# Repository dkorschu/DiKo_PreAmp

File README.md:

# $\text{-DIKO-}\sqrt{\text{REGGAE}}\text{-PREAMP-}$

[English version below](#english-version)

Dieses Repository zeigt die Entwicklung des DIKO ELEKTROTECHNIK Vorverstärkers, vom ersten Prototyp bis zum aktuellen Stand.

## Ordnerstruktur

- Blockschaltbilder
- Ältere Versionen
- KiCad Dateien
- Bilder
- Datenblätter
- 3D Druck

## Version 1

Version 1 entstand im Rahmen meiner Bachelorarbeit. Schaltpläne und Fertigungsdateien der Platinen wurden mit Altium Designer erstellt. Das Besondere an dieser Version: Die analoge Frequenzweiche lässt sich über Digitalpotentiometer einstellen.

**Hinweis: Version 1 ist fehlerhaft!**

## Version 2

Version 2 baut auf den Erkenntnissen aus Version 1 auf und bringt komplett neue Platinen mit. Die Digitalpotentiometer sind entfallen, da der Vorverstärker einfacher werden und der Fokus zunächst auf der analogen Schaltungstechnik liegen sollte. Zur Berechnung der Frequenzweiche wurden außerdem Jupyter Notebooks eingesetzt, die sehr gute Ergebnisse geliefert haben.

Bei den bisherigen Tests wurden schaltungstechnisch keine Fehler gefunden. Trotzdem gibt es zwei Schwachstellen:

- Das Platinenlayout ist nicht zufriedenstellend.
- Der Mikrofonvorverstärker verstärkt das Signal nicht ausreichend.

Aus diesen Gründen wird nun an Version 3 gearbeitet.

## Version 3

Version 3 teilt den Vorverstärker in einzelne Komponenten auf, die sich miteinander verbinden lassen.

2026_10_05 Den Anfang macht die Frequenzweiche, die sich auch eigenständig mit einem externen Mischpult nutzen lässt.

---

# English Version

This repository documents the development of the DIKO ELEKTROTECHNIK preamplifier, from the first prototype to the current state.

## Folder Structure

- Blockschaltbilder (block diagrams)
- Ältere Versionen (older versions)
- KiCad Dateien (KiCad files)
- Bilder (images)
- Datenblätter (datasheets)
- 3D Druck (3D printing)

## Version 1
Version 1 was developed as part of my bachelor's thesis. The schematics and PCB manufacturing files were created with Altium Designer. What makes this version special: the analog crossover can be adjusted using digital potentiometers.

**Note: Version 1 is faulty!**

## Version 2

Version 2 builds on the findings from Version 1 and comes with completely new PCBs. The digital potentiometers were removed to make the preamp simpler and to focus on the analog circuitry first. In addition, Jupyter Notebooks were used to calculate the crossover, with very good results.

So far, testing has not revealed any circuit errors. However, there are two weak points:

- The PCB layout is not satisfactory.
- The microphone preamp does not amplify the signal sufficiently.

For these reasons, work is now underway on Version 3.

## Version 3

Version 3 splits the preamp into individual components that can be connected to each other.

2026_10_05 The first step is the crossover, which can also be used on its own with an external mixing console.

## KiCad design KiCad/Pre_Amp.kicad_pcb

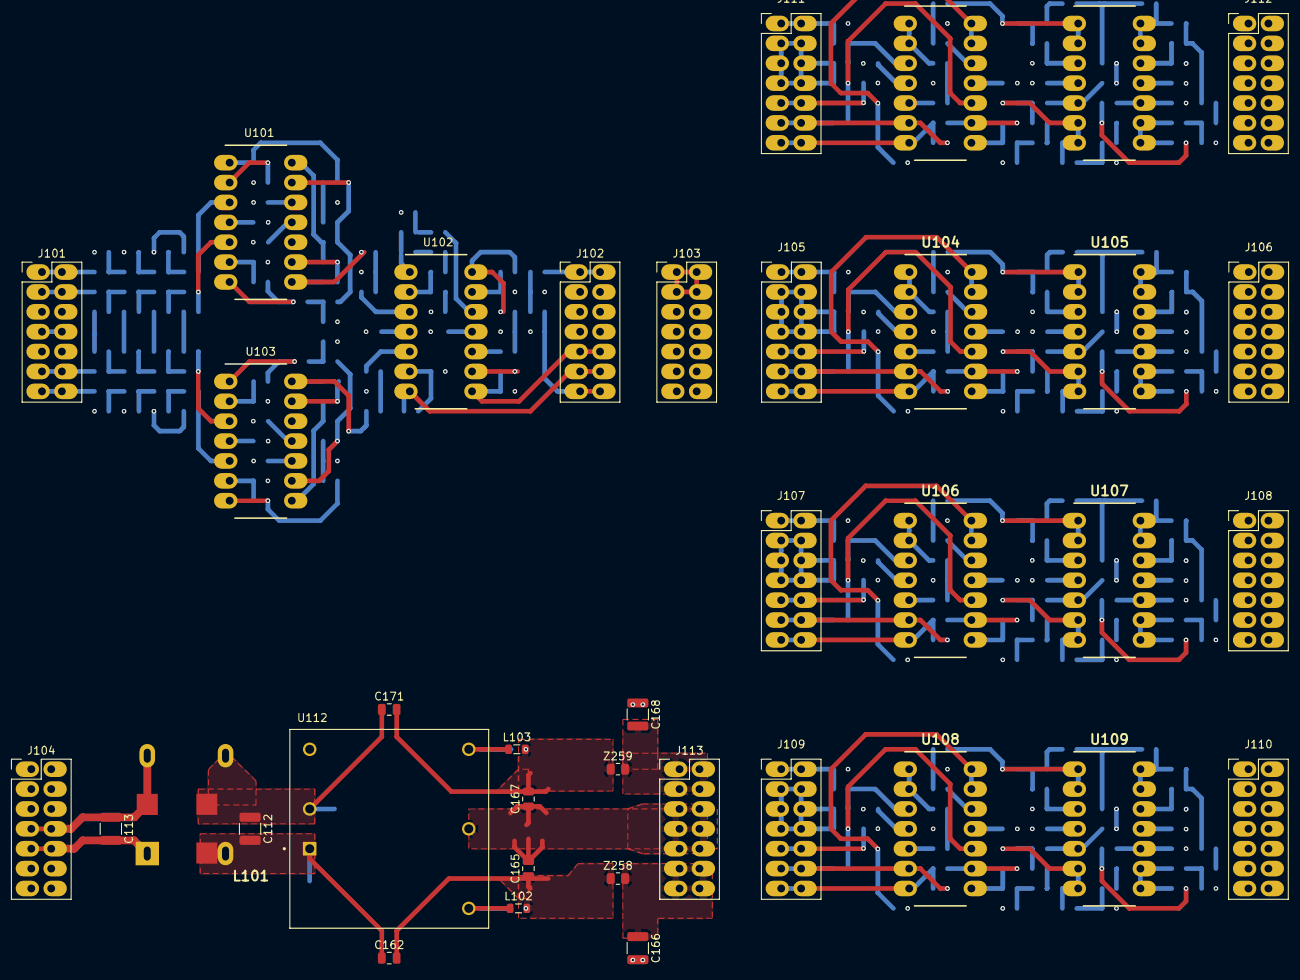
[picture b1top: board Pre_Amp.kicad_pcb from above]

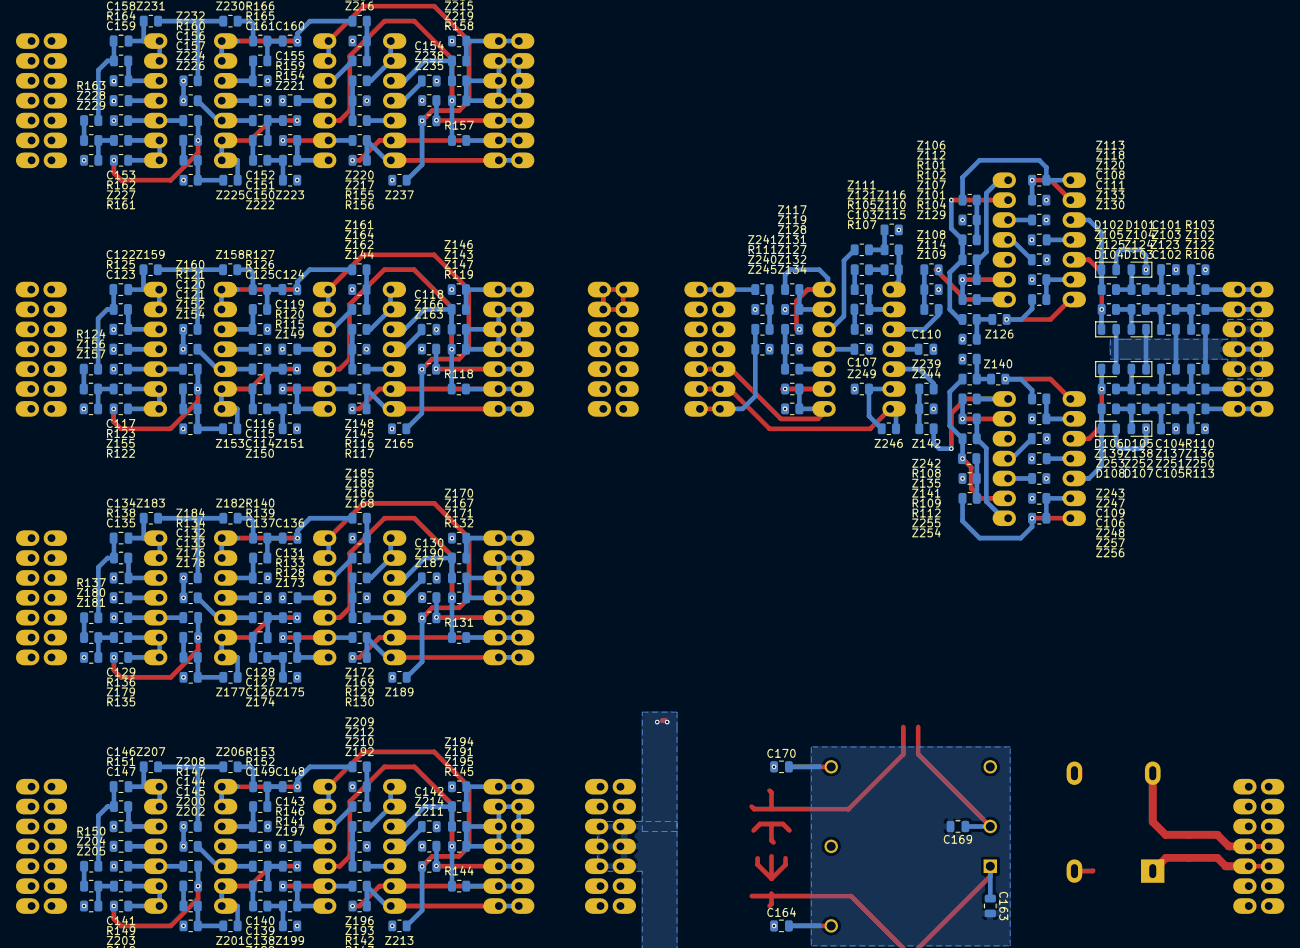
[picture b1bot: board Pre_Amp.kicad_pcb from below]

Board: 4 copper layers, 331 parts (293 on the bottom side), 210 nets.

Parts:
C101, C102, C104, C105, C114, C115, C126, C127, C138, C139, C150, C151, C163, C169: 10n; C_0805_2012Metric
C103: 47u; C_0805_2012Metric
C106, C107, C108, C109, C110, C111, C116, C117, C118, C119, C125, C128, C129, C130, C131, C137, C140, C141, C142, C143, C149, C152, C153, C154, C155, C161, C165, C167: 100n; C_0805_2012Metric
C112, C113, C166, C168: 10u; C_1210_3225Metric
C120, C121, C132, C133, C144, C145, C156, C157: 220n; C_0805_2012Metric
C122, C123, C134, C135, C146, C147, C158, C159: 150n; C_0805_2012Metric
C124, C136, C148, C160: 1u; C_0805_2012Metric
C162, C171: 470p; C_0805_2012Metric
C164, C170: 1n; C_0805_2012Metric
D101, D102, D103, D104, D105, D106, D107, D108: D; D_0805_2012Metric
J101: Stecker_4In; PinHeader_2x07_P2.54mm_Vertical
J102: Stecker_1Out_Switch; PinHeader_2x07_P2.54mm_Vertical
J103, J106, J108, J110, J112: Conn_02x07_Odd_Even; PinHeader_2x07_P2.54mm_Vertical
J104: Stecker_1In_2Switch; PinHeader_2x07_P2.54mm_Vertical
J105, J107, J109, J111: Stecker_In_Out_Switch; PinHeader_2x07_P2.54mm_Vertical
J113: VCC; PinHeader_2x07_P2.54mm_Vertical
L101: WE-SL575
L102, L103: Dämpfungsperle, 220 Ohm @ 100MHz, 0.5A; L_0805_2012Metric
R101, R102, R104, R108, R109, R112, R122, R135, R148, R161: 10k; R_0805_2012Metric
R103, R106, R110, R111, R113: 390k; R_0805_2012Metric
R105: 33k; R_0805_2012Metric
R107, R116, R117, R118, R129, R130, R131, R142, R143, R144, R155, R156, R157: 1k; R_0805_2012Metric
R115, R119, R128, R132, R141, R145, R154, R158: 100k; R_0805_2012Metric
R120, R133, R146, R159: 560k; R_0805_2012Metric
R121, R134, R147, R160: 680k; R_0805_2012Metric
R123, R136, R149, R162: 75k; R_0805_2012Metric
R124, R125, R137, R138, R150, R151, R163, R164: 15k; R_0805_2012Metric
R126, R127, R139, R140, R152, R153, R165, R166: 7k5; R_0805_2012Metric
U101, U102, U103, U104, U105, U106, U107, U108, U109, U110, U111: TL074; DIP794W53P254L1930H508Q14N
U112: REC10K-2415; CONV_REC10K-2415DAW_H2
Z101, Z102, Z103, Z104, Z105, Z106, Z107, Z112, Z113, Z117, Z118, Z119, Z120, Z122, Z123, Z124, Z125, Z126, Z129, Z130, Z132, Z133, Z134, Z135, Z136, Z137, Z138, Z139, Z140, Z141, Z146, Z148, Z151, Z154, Z160, Z165, Z170, Z172, Z175, Z178, Z184, Z189, Z194, Z196, Z199, Z202, Z208, Z213, Z218, Z220, Z223, Z226, Z232, Z237, Z240, Z241, Z242, Z243, Z245, Z246, Z247, Z248, Z249, Z250, Z251, Z252, Z253, Z254, Z255, Z256, Z257: R_0805_2012Metric
Z108, Z109, Z110, Z111, Z127, Z128, Z142, Z144, Z145, Z149, Z150, Z152, Z153, Z155, Z156, Z158, Z159, Z161, Z162, Z168, Z169, Z173, Z174, Z176, Z177, Z179, Z180, Z182, Z183, Z185, Z186, Z192, Z193, Z197, Z198, Z200, Z201, Z203, Z204, Z206, Z207, Z209, Z210, Z216, Z217, Z221, Z222, Z224, Z225, Z227, Z228, Z230, Z231, Z233, Z234, Z239, Z258, Z259: 0R; R_0805_2012Metric
Z114, Z116, Z131, Z157, Z164, Z181, Z188, Z205, Z212, Z229, Z236, Z244: 820k; R_0805_2012Metric
Z115: 390k/10n; R_0805_2012Metric
Z121: 33k/2n2; R_0805_2012Metric
Z143, Z163, Z167, Z187, Z191, Z211, Z215, Z235: 1u; R_0805_2012Metric
Z147, Z166, Z171, Z190, Z195, Z214, Z219, Z238: 100k; R_0805_2012Metric

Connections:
+15V: C106.2, C108.2, C110.2, C116.2, C118.2, C128.2, C130.2, C140.2, C142.2, C152.2, C154.2, C166.1, J103.11, J103.12, J103.13, J103.14, J106.11, J106.12, J106.13, J106.14, J108.11, J108.12, J108.13, J108.14, J110.11, J110.12, J110.13, J110.14, J112.11, J112.12, J112.13, J112.14, J113.11 (+15V), J113.12 (+15V), J113.13 (+15V), J113.14 (+15V), U101.4 (V+), U102.4 (V+), U103.4 (V+), U104.4 (V+), U105.4 (V+), U106.4 (V+), U107.4 (V+), U108.4 (V+), U109.4 (V+), U110.4 (V+), U111.4 (V+), Z258.2
-15V: C107.2, C109.2, C111.2, C117.2, C119.2, C129.2, C131.2, C141.2, C143.2, C153.2, C155.2, C168.2, J103.1, J103.2, J103.3, J103.4, J106.1, J106.2, J106.3, J106.4, J108.1, J108.2, J108.3, J108.4, J110.1, J110.2, J110.3, J110.4, J112.1, J112.2, J112.3, J112.4, J113.1 (-15V), J113.2 (-15V), J113.3 (-15V), J113.4 (-15V), U101.11 (V-), U102.11 (V-), U103.11 (V-), U104.11 (V-), U105.11 (V-), U106.11 (V-), U107.11 (V-), U108.11 (V-), U109.11 (V-), U110.11 (V-), U111.11 (V-), Z259.2
GND: C101.1, C102.1, C104.1, C105.1, C106.1, C107.1, C108.1, C109.1, C110.1, C111.1, C116.1, C117.1, C118.1, C119.1, C123.1, C125.1, C128.1, C129.1, C130.1, C131.1, C135.1, C137.1, C140.1, C141.1, C142.1, C143.1, C147.1, C149.1, C152.1, C153.1, C154.1, C155.1, C159.1, C161.1, C165.2, C166.2, C167.1, C168.1, D101.1 (K), D102.2 (A), D103.1 (K), D104.2 (A), D105.1 (K), D106.2 (A), D107.1 (K), D108.2 (A), J101.5 (GND), J101.6 (GND), J101.7 (GND), J101.8 (GND), J101.9 (GND), J101.10 (GND), J102.3 (GND), J102.4 (GND), J102.5 (GND), J102.6 (GND), J102.7 (GND), J102.8 (GND), J103.5, J103.6, J103.7, J103.8, J103.9, J103.10, J105.3, J105.4, J105.5, J105.6, J105.7, J105.8, J106.5, J106.6, J106.7, J106.8, J106.9, J106.10, J107.3, J107.4, J107.5, J107.6, J107.7, J107.8, J108.5, J108.6, J108.7, J108.8, J108.9, J108.10, J109.3, J109.4, J109.5, J109.6, J109.7, J109.8, J110.5, J110.6, J110.7, J110.8, J110.9, J110.10, J111.3, J111.4, J111.5, J111.6, J111.7, J111.8, J112.5, J112.6, J112.7, J112.8, J112.9, J112.10, J113.5 (GND), J113.6 (GND), J113.7 (GND), J113.8 (GND), J113.9 (GND), J113.10 (GND), R103.2, R106.2, R107.1, R110.2, R111.2, R113.2, R119.1, R121.1, R123.1, R132.1, R134.1, R136.1, R145.1, R147.1, R149.1, R158.1, R160.1, R162.1, U101.10 (+), U103.12 (+), U112.5 (COM), Z112.2, Z114.2, Z116.2, Z118.2, Z119.2, Z120.2, Z129.2, Z131.2, Z133.2, Z134.2, Z146.2, Z147.2, Z148.2, Z151.2, Z154.2, Z157.2, Z160.2, Z164.2, Z165.2, Z166.2, Z170.2, Z171.2, Z172.2, Z175.2, Z178.2, Z181.2, Z184.2, Z188.2, Z189.2, Z190.2, Z194.2, Z195.2, Z196.2, Z199.2, Z202.2, Z205.2, Z208.2, Z212.2, Z213.2, Z214.2, Z218.2, Z219.2, Z220.2, Z223.2, Z226.2, Z229.2, Z232.2, Z236.2, Z237.2, Z238.2, Z242.2, Z244.2, Z245.2, Z247.2, Z248.2, Z249.2, Z255.2, Z257.2
GND_FILT: C163.2, C164.2, C169.2, C170.2
unnamed: C101.2, Z103.2, Z104.1
unnamed: C102.2, Z123.2, Z124.1
unnamed: C103.1, R107.2
unnamed: C104.2, Z137.2, Z138.1
unnamed: C105.2, Z251.2, Z252.1
unnamed: C113.1, J104.7 (SW_2), J104.8 (SW_2), L101.4
unnamed: C113.2, J104.9 (SW_4), J104.10 (SW_4), L101.1
unnamed: C114.1, Z150.1
unnamed: C114.2, C115.1, R120.1
unnamed: C120.1, C121.2, R122.1
unnamed: C121.1, Z152.2
unnamed: C122.1, R124.2, R125.1
unnamed: C124.1, R126.1, R127.2
unnamed: C126.1, Z174.1
unnamed: C126.2, C127.1, R133.1
unnamed: C132.1, C133.2, R135.1
unnamed: C133.1, Z176.2
unnamed: C134.1, R137.2, R138.1
unnamed: C136.1, R139.1, R140.2
unnamed: C138.1, Z198.1
unnamed: C138.2, C139.1, R146.1
unnamed: C144.1, C145.2, R148.1
unnamed: C145.1, Z200.2
unnamed: C146.1, R150.2, R151.1
unnamed: C148.1, R152.1, R153.2
unnamed: C150.1, Z222.1
unnamed: C150.2, C151.1, R159.1
unnamed: C156.1, C157.2, R161.1
unnamed: C157.1, Z224.2
unnamed: C158.1, R163.2, R164.1
unnamed: C160.1, R165.1, R166.2
unnamed: C162.2, C164.1, C165.1, L102.2, Z258.1
unnamed: C167.2, C170.1, C171.2, L103.2, Z259.1
unnamed: D101.2 (A), Z104.2, Z105.1
unnamed: D102.1 (K), U101.3 (+), Z105.2
unnamed: D103.2 (A), Z124.2, Z125.1
unnamed: D104.1 (K), U101.5 (+), Z125.2
unnamed: D105.2 (A), Z138.2, Z139.1
unnamed: D106.1 (K), U103.3 (+), Z139.2
unnamed: D107.2 (A), Z252.2, Z253.1
unnamed: D108.1 (K), U103.5 (+), Z253.2
unnamed: J101.1 (Phono_L), J101.2, Z102.1
unnamed: J101.3 (Phono_R), J101.4 (Phono_R), Z122.1
unnamed: J101.11 (Line_L), J101.12 (Line_L), Z136.1
unnamed: J101.13 (Line_R), J101.14 (Line_R), Z250.1
unnamed: J102.9 (SW_In1), J102.10 (SW_2), U102.8, Z132.2, Z134.1
unnamed: J102.11 (SW_In2), J102.12 (SW_3), U102.7, Z246.1
unnamed: J102.13 (SW_Out), J102.14 (SW_Out), Z240.2, Z245.1
unnamed: J104.3 (VCC_GND), J104.4 (VCC_GND), J104.5 (VCC_GND), J104.6 (VCC_GND), J104.11 (SW_1), J104.12 (SW_1)
unnamed: J104.1 (VCC_In), J104.2 (VCC_In), J104.13 (SW_3), J104.14 (SW_3)
unnamed: J102.1 (Out), J102.2 (Out), J105.1, J105.2, J107.1, J107.2, J109.1, J109.2, J111.1, J111.2, Z143.2, Z146.1, Z167.2, Z170.1, Z191.2, Z194.1, Z215.2, Z218.1, Z241.1
unnamed: J105.9, J105.10, Z163.2, Z166.1
unnamed: J105.11 (SW_In), J105.12, R117.1, R118.1, U104.6 (-)
unnamed: J105.13 (SW_Out), J105.14, R116.1, R117.2, U104.7
unnamed: J107.9, J107.10, Z187.2, Z190.1
unnamed: J107.11 (SW_In), J107.12, R130.1, R131.1, U106.6 (-)
unnamed: J107.13 (SW_Out), J107.14, R129.1, R130.2, U106.7
unnamed: J109.9, J109.10, Z211.2, Z214.1
unnamed: J109.11 (SW_In), J109.12, R143.1, R144.1, U108.6 (-)
unnamed: J109.13 (SW_Out), J109.14, R142.1, R143.2, U108.7
unnamed: J111.9, J111.10, Z235.2, Z238.1
unnamed: J111.11 (SW_In), J111.12, R156.1, R157.1, U110.6 (-)
unnamed: J111.13 (SW_Out), J111.14, R155.1, R156.2, U110.7
unnamed: R101.1, Z106.2, Z112.1
unnamed: R102.2, U101.14, Z107.2
unnamed: R103.1, Z102.2, Z103.1
unnamed: R104.1, Z126.2, Z129.1
unnamed: R105.1, Z121.2
unnamed: R106.1, Z122.2, Z123.1
unnamed: R108.1, Z140.2, Z242.1
unnamed: R109.2, U103.8, Z141.2
unnamed: R110.1, Z136.2, Z137.1
unnamed: R111.1, Z240.1, Z241.2
unnamed: R112.1, Z254.2, Z255.1
unnamed: R113.1, Z250.2, Z251.1
unnamed: R115.2, U104.8, Z149.2
unnamed: R124.1, Z156.1
unnamed: R127.1, Z158.2
unnamed: R128.2, U106.8, Z173.2
unnamed: R137.1, Z180.1
unnamed: R140.1, Z182.2
unnamed: R141.2, U108.8, Z197.2
unnamed: R150.1, Z204.1
unnamed: R153.1, Z206.2
unnamed: R154.2, U110.8, Z221.2
unnamed: R163.1, Z228.1
unnamed: R166.1, Z230.2
unnamed: U101.1, Z106.1, Z113.1
unnamed: U101.7, Z126.1, Z130.1
unnamed: U101.8, Z101.1, Z108.1
unnamed: U101.2 (-), Z113.2, Z118.1
unnamed: U101.6 (-), Z130.2, Z133.1
unnamed: U101.9 (-), Z101.2, Z107.1
unnamed: U101.12 (+), Z120.1
unnamed: R101.2, R102.1, R104.2, U101.13 (-)
unnamed: U102.1, Z110.1, Z115.1
unnamed: U102.14, Z117.1, Z128.1
unnamed: U102.3 (+), Z109.2
unnamed: C103.2, R105.2, U102.2 (-)
unnamed: U102.5 (+), Z239.2
unnamed: U102.6 (-), Z246.2, Z249.1
unnamed: U102.10 (+), Z127.2
unnamed: U102.9 (-), Z132.1
unnamed: U102.12 (+), Z111.2
unnamed: U102.13 (-), Z117.2, Z119.1
unnamed: U103.1, Z140.1, Z243.1
unnamed: U103.7, Z254.1, Z256.1
unnamed: U103.14, Z135.1, Z142.1
unnamed: U103.2 (-), Z243.2, Z247.1
unnamed: U103.6 (-), Z256.2, Z257.1
unnamed: U103.10 (+), Z248.1
unnamed: R108.2, R109.1, R112.2, U103.9 (-)
unnamed: U103.13 (-), Z135.2, Z141.1
unnamed: U104.3 (+), Z143.1, Z147.1
unnamed: U104.1, U104.2 (-), Z144.2
unnamed: U104.5 (+), Z145.1
unnamed: R118.2, R119.2, U104.10 (+)
unnamed: R115.1, R116.2, U104.9 (-)
unnamed: U104.12 (+), Z162.2
unnamed: U104.13 (-), U104.14, Z163.1, Z165.1
unnamed: C125.2, R126.2, U105.3 (+)
unnamed: C124.2, U105.1, U105.2 (-), Z161.1
unnamed: C115.2, R121.2, U105.5 (+)
unnamed: R120.2, U105.6 (-), U105.7, Z153.1
unnamed: C120.2, R123.2, U105.10 (+)
unnamed: R122.2, U105.8, U105.9 (-), Z155.2
unnamed: C123.2, R125.2, U105.12 (+)
unnamed: C122.2, U105.13 (-), U105.14, Z159.1
unnamed: U106.3 (+), Z167.1, Z171.1
unnamed: U106.1, U106.2 (-), Z168.2
unnamed: U106.5 (+), Z169.1
unnamed: R131.2, R132.2, U106.10 (+)
unnamed: R128.1, R129.2, U106.9 (-)
unnamed: U106.12 (+), Z186.2
unnamed: U106.13 (-), U106.14, Z187.1, Z189.1
unnamed: C137.2, R139.2, U107.3 (+)
unnamed: C136.2, U107.1, U107.2 (-), Z185.1
unnamed: C127.2, R134.2, U107.5 (+)
unnamed: R133.2, U107.6 (-), U107.7, Z177.1
unnamed: C132.2, R136.2, U107.10 (+)
unnamed: R135.2, U107.8, U107.9 (-), Z179.2
unnamed: C135.2, R138.2, U107.12 (+)
unnamed: C134.2, U107.13 (-), U107.14, Z183.1
unnamed: U108.3 (+), Z191.1, Z195.1
unnamed: U108.1, U108.2 (-), Z192.2
unnamed: U108.5 (+), Z193.1
unnamed: R144.2, R145.2, U108.10 (+)
unnamed: R141.1, R142.2, U108.9 (-)
unnamed: U108.12 (+), Z210.2
unnamed: U108.13 (-), U108.14, Z211.1, Z213.1
unnamed: C149.2, R152.2, U109.3 (+)
unnamed: C148.2, U109.1, U109.2 (-), Z209.1
unnamed: C139.2, R147.2, U109.5 (+)
unnamed: R146.2, U109.6 (-), U109.7, Z201.1
unnamed: C144.2, R149.2, U109.10 (+)
unnamed: R148.2, U109.8, U109.9 (-), Z203.2
unnamed: C147.2, R151.2, U109.12 (+)
unnamed: C146.2, U109.13 (-), U109.14, Z207.1
unnamed: U110.3 (+), Z215.1, Z219.1
unnamed: U110.1, U110.2 (-), Z216.2
unnamed: U110.5 (+), Z217.1
unnamed: R157.2, R158.2, U110.10 (+)
unnamed: R154.1, R155.2, U110.9 (-)
unnamed: U110.12 (+), Z234.2
unnamed: U110.13 (-), U110.14, Z235.1, Z237.1
unnamed: C161.2, R165.2, U111.3 (+)
unnamed: C160.2, U111.1, U111.2 (-), Z233.1
unnamed: C151.2, R160.2, U111.5 (+)
unnamed: R159.2, U111.6 (-), U111.7, Z225.1
unnamed: C156.2, R162.2, U111.10 (+)
unnamed: R161.2, U111.8, U111.9 (-), Z227.2
unnamed: C159.2, R164.2, U111.12 (+)
unnamed: C158.2, U111.13 (-), U111.14, Z231.1
unnamed: C112.2, C162.1, C163.1, L101.2, U112.1 (+VIN)
unnamed: L102.1, U112.6 (+VOUT)
unnamed: C112.1, C169.1, C171.1, L101.3, U112.2 (-VIN)
unnamed: L103.1, U112.4 (-VOUT)
unnamed: Z108.2, Z109.1, Z114.1
unnamed: Z110.2, Z111.1, Z116.1
unnamed: Z115.2, Z121.1
unnamed: Z127.1, Z128.2, Z131.1
unnamed: Z142.2, Z239.1, Z244.1
unnamed: Z144.1, Z145.2, Z148.1
unnamed: Z149.1, Z150.2, Z151.1
unnamed: Z152.1, Z153.2, Z154.1
unnamed: Z155.1, Z156.2, Z157.1
unnamed: Z158.1, Z159.2, Z160.1
unnamed: Z161.2, Z162.1, Z164.1
unnamed: Z168.1, Z169.2, Z172.1
unnamed: Z173.1, Z174.2, Z175.1
unnamed: Z176.1, Z177.2, Z178.1
unnamed: Z179.1, Z180.2, Z181.1
unnamed: Z182.1, Z183.2, Z184.1
unnamed: Z185.2, Z186.1, Z188.1
unnamed: Z192.1, Z193.2, Z196.1
unnamed: Z197.1, Z198.2, Z199.1
unnamed: Z200.1, Z201.2, Z202.1
unnamed: Z203.1, Z204.2, Z205.1
unnamed: Z206.1, Z207.2, Z208.1
unnamed: Z209.2, Z210.1, Z212.1
unnamed: Z216.1, Z217.2, Z220.1
unnamed: Z221.1, Z222.2, Z223.1
unnamed: Z224.1, Z225.2, Z226.1
unnamed: Z227.1, Z228.2, Z229.1
unnamed: Z230.1, Z231.2, Z232.1
unnamed: Z233.2, Z234.1, Z236.1

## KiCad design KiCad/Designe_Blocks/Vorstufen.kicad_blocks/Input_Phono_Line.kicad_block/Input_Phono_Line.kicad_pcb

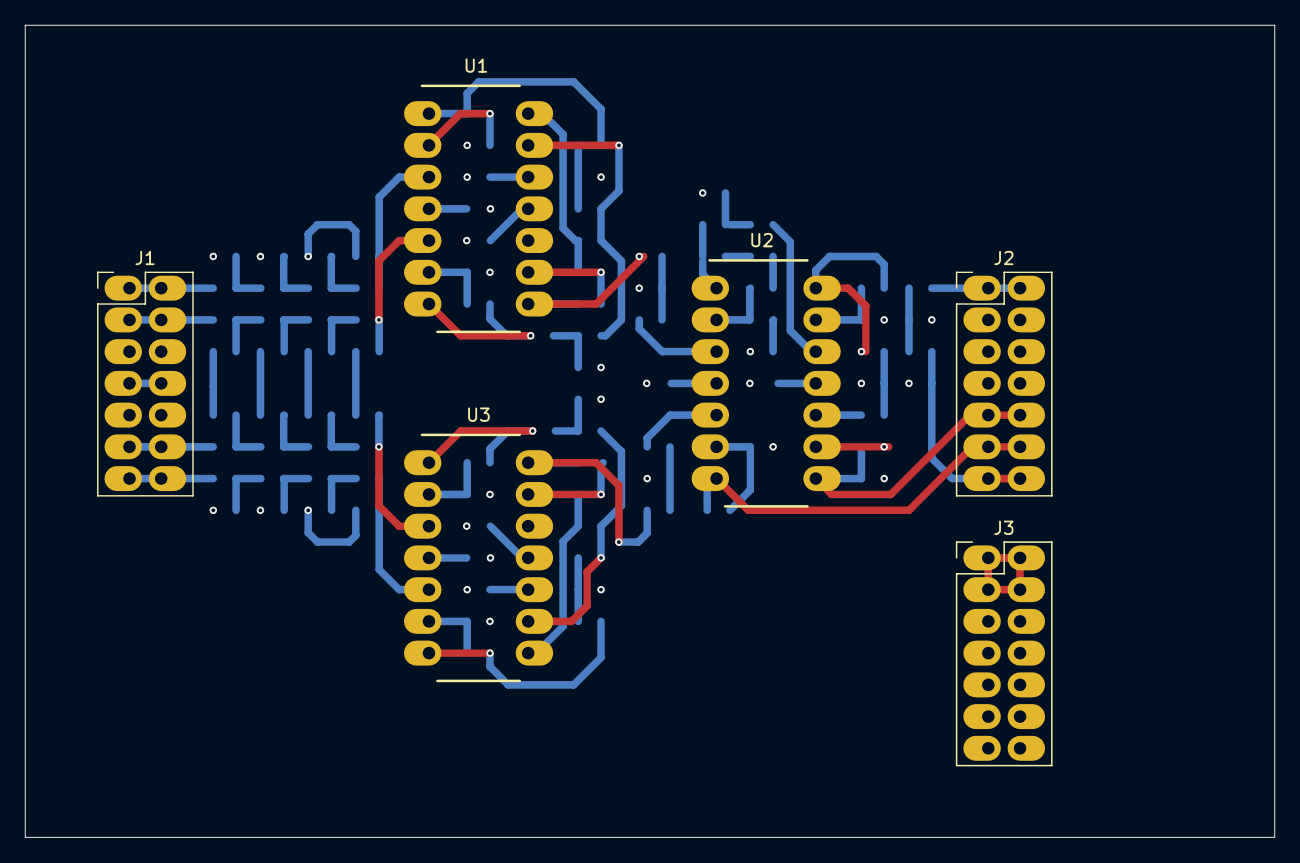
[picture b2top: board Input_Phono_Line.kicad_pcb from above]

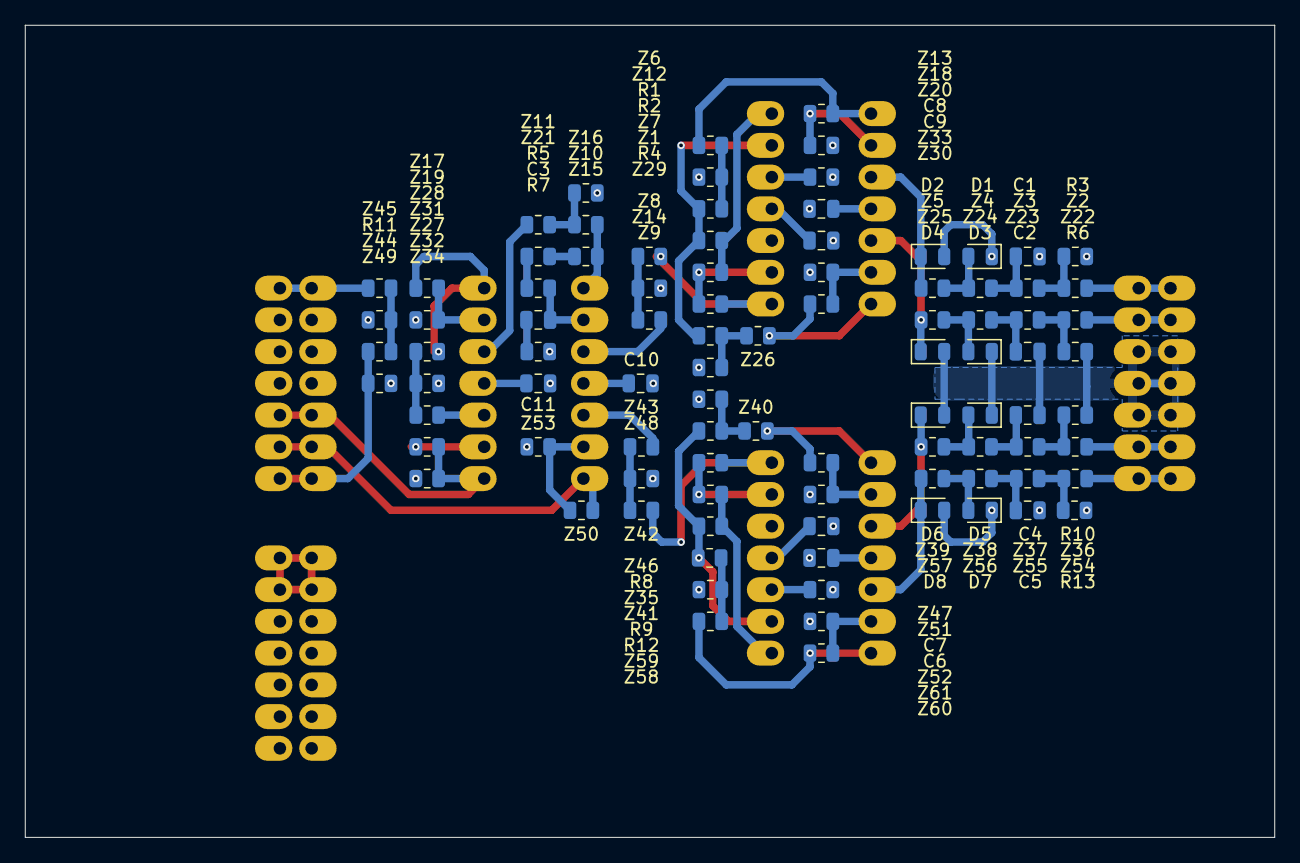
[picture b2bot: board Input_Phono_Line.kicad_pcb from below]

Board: 4 copper layers, 100.0 x 65.0 mm, 99 parts (93 on the bottom side), 67 nets.

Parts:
C1, C2, C4, C5: 10n; C_0805_2012Metric
C3: 47u; C_0805_2012Metric
C6, C7, C8, C9, C10, C11: 100n; C_0805_2012Metric
D1, D2, D3, D4, D5, D6, D7, D8: D; D_0805_2012Metric
J1: Stecker_4In; PinHeader_2x07_P2.54mm_Vertical
J2: Stecker_1Out_Switch; PinHeader_2x07_P2.54mm_Vertical
J3: Conn_02x07_Odd_Even; PinHeader_2x07_P2.54mm_Vertical
R1, R2, R4, R8, R9, R12: 10k; R_0805_2012Metric
R3, R6, R10, R11, R13: 390k; R_0805_2012Metric
R5: 33k; R_0805_2012Metric
R7: 1k; R_0805_2012Metric
U1, U2, U3: TL074; DIP794W53P254L1930H508Q14N
Z1, Z2, Z3, Z4, Z5, Z6, Z7, Z12, Z13, Z17, Z18, Z19, Z20, Z22, Z23, Z24, Z25, Z26, Z29, Z30, Z32, Z33, Z34, Z35, Z36, Z37, Z38, Z39, Z40, Z41, Z44, Z45, Z46, Z47, Z49, Z50, Z51, Z52, Z53, Z54, Z55, Z56, Z57, Z58, Z59, Z60, Z61: R_0805_2012Metric
Z8, Z9, Z10, Z11, Z27, Z28, Z42, Z43: 0R; R_0805_2012Metric
Z14, Z16, Z31, Z48: 820k; R_0805_2012Metric
Z15: 390k/10n; R_0805_2012Metric
Z21: 33k/2n2; R_0805_2012Metric

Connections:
+15V: C6.2, C8.2, C10.2, J3.11, J3.12, J3.13, J3.14, U1.4 (V+), U2.4 (V+), U3.4 (V+)
-15V: C7.2, C9.2, C11.2, J3.1, J3.2, J3.3, J3.4, U1.11 (V-), U2.11 (V-), U3.11 (V-)
GND: C1.1, C2.1, C4.1, C5.1, C6.1, C7.1, C8.1, C9.1, C10.1, C11.1, D1.1 (K), D2.2 (A), D3.1 (K), D4.2 (A), D5.1 (K), D6.2 (A), D7.1 (K), D8.2 (A), J1.5 (GND), J1.6 (GND), J1.7 (GND), J1.8 (GND), J1.9 (GND), J1.10 (GND), J2.3 (GND), J2.4 (GND), J2.5 (GND), J2.6 (GND), J2.7 (GND), J2.8 (GND), J3.5, J3.6, J3.7, J3.8, J3.9, J3.10, R3.2, R6.2, R7.1, R10.2, R11.2, R13.2, U1.10 (+), U3.12 (+), Z12.2, Z14.2, Z16.2, Z18.2, Z19.2, Z20.2, Z29.2, Z31.2, Z33.2, Z34.2, Z46.2, Z48.2, Z49.2, Z51.2, Z52.2, Z53.2, Z59.2, Z61.2
unnamed: C1.2, Z3.2, Z4.1
unnamed: C2.2, Z23.2, Z24.1
unnamed: C3.1, R7.2
unnamed: C4.2, Z37.2, Z38.1
unnamed: C5.2, Z55.2, Z56.1
unnamed: D1.2 (A), Z4.2, Z5.1
unnamed: D2.1 (K), U1.3 (+), Z5.2
unnamed: D3.2 (A), Z24.2, Z25.1
unnamed: D4.1 (K), U1.5 (+), Z25.2
unnamed: D5.2 (A), Z38.2, Z39.1
unnamed: D6.1 (K), U3.3 (+), Z39.2
unnamed: D7.2 (A), Z56.2, Z57.1
unnamed: D8.1 (K), U3.5 (+), Z57.2
unnamed: J1.1 (Phono_L), J1.2, Z2.1
unnamed: J1.3 (Phono_R), J1.4 (Phono_R), Z22.1
unnamed: J1.11 (Line_L), J1.12 (Line_L), Z36.1
unnamed: J1.13 (Line_R), J1.14 (Line_R), Z54.1
unnamed: J2.9 (SW_In1), J2.10 (SW_2), U2.8, Z32.2, Z34.1
unnamed: J2.11 (SW_In2), J2.12 (SW_3), U2.7, Z50.1
unnamed: J2.13 (SW_Out), J2.14 (SW_Out), Z44.2, Z49.1
unnamed: J2.1 (Out), J2.2 (Out), Z45.1
unnamed: R1.1, Z6.2, Z12.1
unnamed: R2.2, U1.14, Z7.2
unnamed: R3.1, Z2.2, Z3.1
unnamed: R4.1, Z26.2, Z29.1
unnamed: R5.1, Z21.2
unnamed: R6.1, Z22.2, Z23.1
unnamed: R8.1, Z40.2, Z46.1
unnamed: R9.2, U3.8, Z41.2
unnamed: R10.1, Z36.2, Z37.1
unnamed: R11.1, Z44.1, Z45.2
unnamed: R12.1, Z58.2, Z59.1
unnamed: R13.1, Z54.2, Z55.1
unnamed: U1.1, Z6.1, Z13.1
unnamed: U1.7, Z26.1, Z30.1
unnamed: U1.8, Z1.1, Z8.1
unnamed: U1.2 (-), Z13.2, Z18.1
unnamed: U1.6 (-), Z30.2, Z33.1
unnamed: U1.9 (-), Z1.2, Z7.1
unnamed: U1.12 (+), Z20.1
unnamed: R1.2, R2.1, R4.2, U1.13 (-)
unnamed: U2.1, Z10.1, Z15.1
unnamed: U2.14, Z17.1, Z28.1
unnamed: U2.3 (+), Z9.2
unnamed: C3.2, R5.2, U2.2 (-)
unnamed: U2.5 (+), Z43.2
unnamed: U2.6 (-), Z50.2, Z53.1
unnamed: U2.10 (+), Z27.2
unnamed: U2.9 (-), Z32.1
unnamed: U2.12 (+), Z11.2
unnamed: U2.13 (-), Z17.2, Z19.1
unnamed: U3.1, Z40.1, Z47.1
unnamed: U3.7, Z58.1, Z60.1
unnamed: U3.14, Z35.1, Z42.1
unnamed: U3.2 (-), Z47.2, Z51.1
unnamed: U3.6 (-), Z60.2, Z61.1
unnamed: U3.10 (+), Z52.1
unnamed: R8.2, R9.1, R12.2, U3.9 (-)
unnamed: U3.13 (-), Z35.2, Z41.1
unnamed: Z10.2, Z11.1, Z16.1
unnamed: Z8.2, Z9.1, Z14.1
unnamed: Z15.2, Z21.1
unnamed: Z27.1, Z28.2, Z31.1
unnamed: Z42.2, Z43.1, Z48.1

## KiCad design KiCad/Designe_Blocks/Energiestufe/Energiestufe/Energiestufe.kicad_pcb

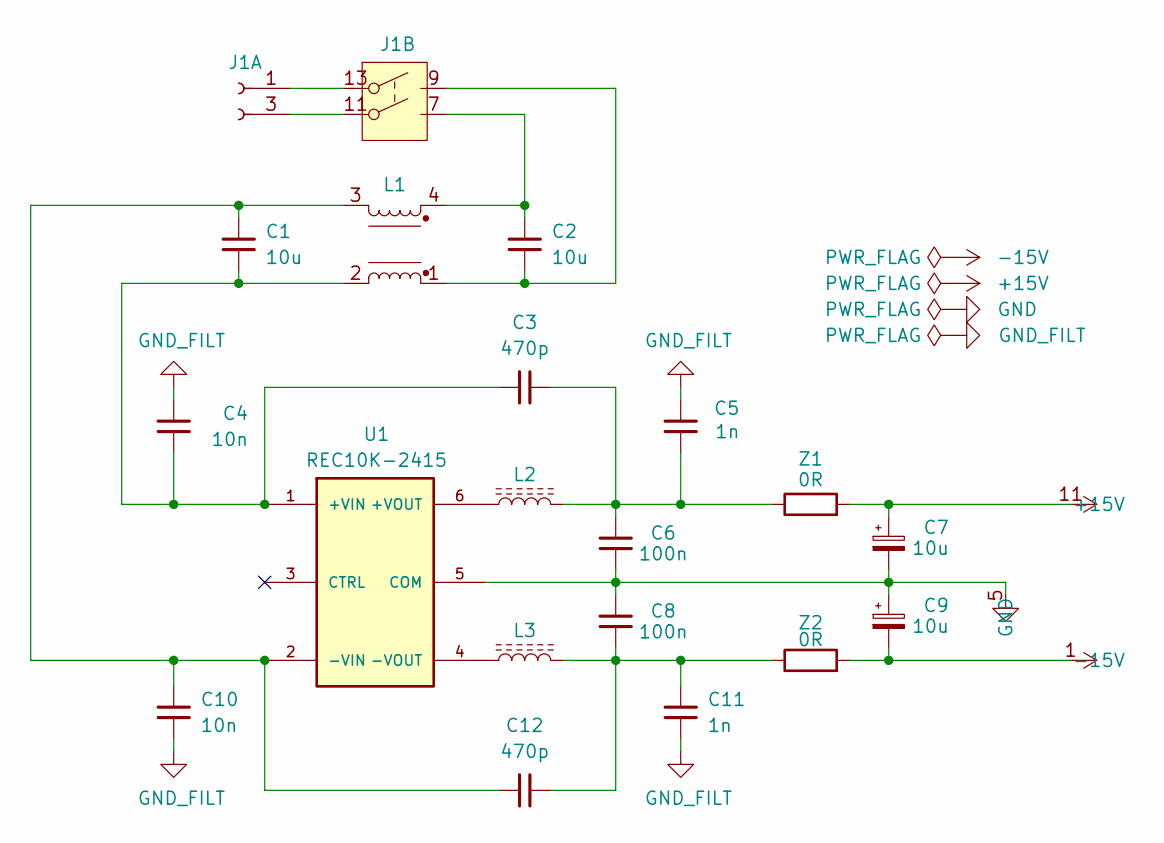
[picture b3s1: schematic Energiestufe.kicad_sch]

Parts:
C1, C2, C7, C9: 10u; C_1210_3225Metric
C3, C12: 470p; C_0805_2012Metric
C4, C10: 10n; C_0805_2012Metric
C5, C11: 1n; C_0805_2012Metric
C6, C8: 100n; C_0805_2012Metric
J1: Stecker_1In_2Switch; PinHeader_2x07_P2.54mm_Vertical
J2: VCC; PinHeader_2x07_P2.54mm_Vertical
L1: WE-SL575
L2, L3: Dämpfungsperle, 220 Ohm @ 100MHz, 0.5A
U1: REC10K-2415; CONV_REC10K-2415DAW_H2; PARTREV PRELIMINARY
Z1, Z2: 0R; R_0805_2012Metric

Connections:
+15V: C7.1, J2.11 (+15V), J2.12 (+15V), J2.13 (+15V), J2.14 (+15V), Z1.2
-15V: C9.2, J2.1 (-15V), J2.2 (-15V), J2.3 (-15V), J2.4 (-15V), Z2.2
GND: C6.2, C7.2, C8.1, C9.1, J2.5 (GND), J2.6 (GND), J2.7 (GND), J2.8 (GND), J2.9 (GND), J2.10 (GND), U1.5 (COM)
GND_FILT: C4.2, C5.2, C10.2, C11.2
unnamed: C2.1, J1.7 (SW_2), J1.8 (SW_2), L1.4
unnamed: C2.2, J1.9 (SW_4), J1.10 (SW_4), L1.1
unnamed: C3.2, C5.1, C6.1, L2.2, Z1.1
unnamed: C8.2, C11.1, C12.2, L3.2, Z2.1
unnamed: J1.3 (VCC_GND), J1.4 (VCC_GND), J1.5 (VCC_GND), J1.6 (VCC_GND), J1.11 (SW_1), J1.12 (SW_1)
unnamed: J1.1 (VCC_In), J1.2 (VCC_In), J1.13 (SW_3), J1.14 (SW_3)
unnamed: C1.2, C3.1, C4.1, L1.2, U1.1 (+VIN)
unnamed: L2.1, U1.6 (+VOUT)
unnamed: C1.1, C10.1, C12.1, L1.3, U1.2 (-VIN)
unnamed: L3.1, U1.4 (-VOUT)

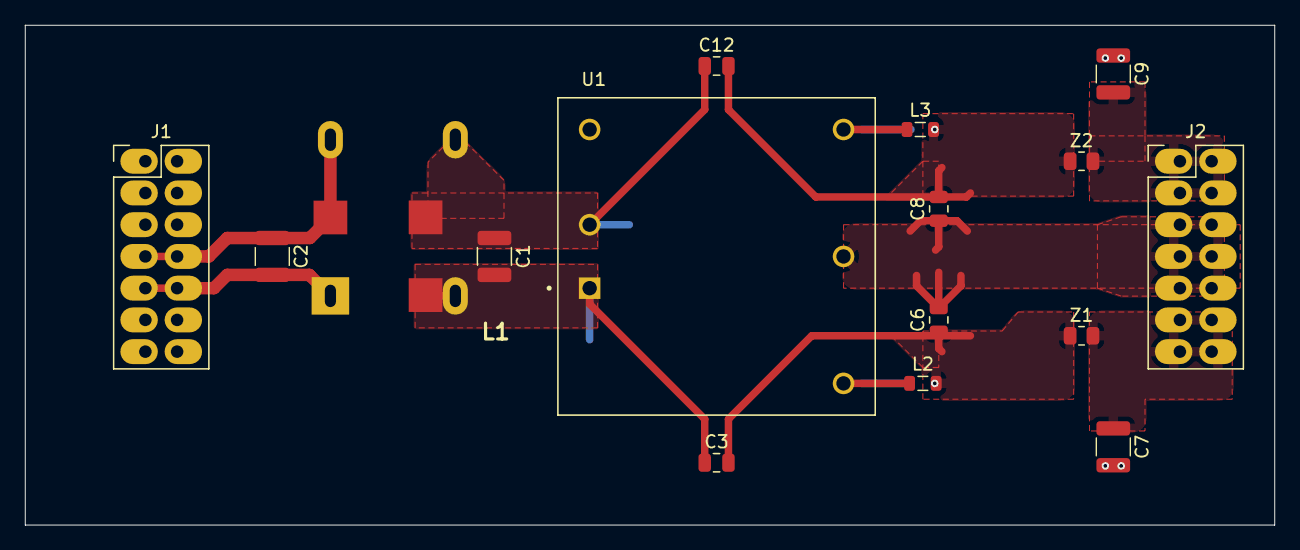
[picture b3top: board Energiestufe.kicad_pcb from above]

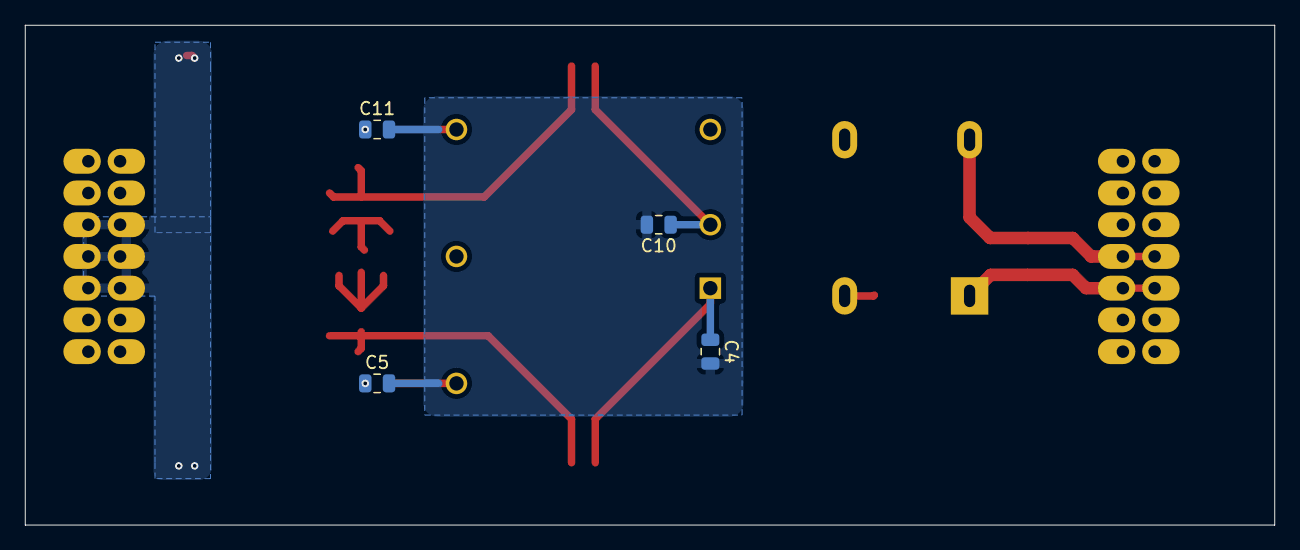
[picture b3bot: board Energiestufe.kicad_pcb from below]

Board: 4 copper layers, 100.0 x 40.0 mm, 20 parts (4 on the bottom side), 14 nets.

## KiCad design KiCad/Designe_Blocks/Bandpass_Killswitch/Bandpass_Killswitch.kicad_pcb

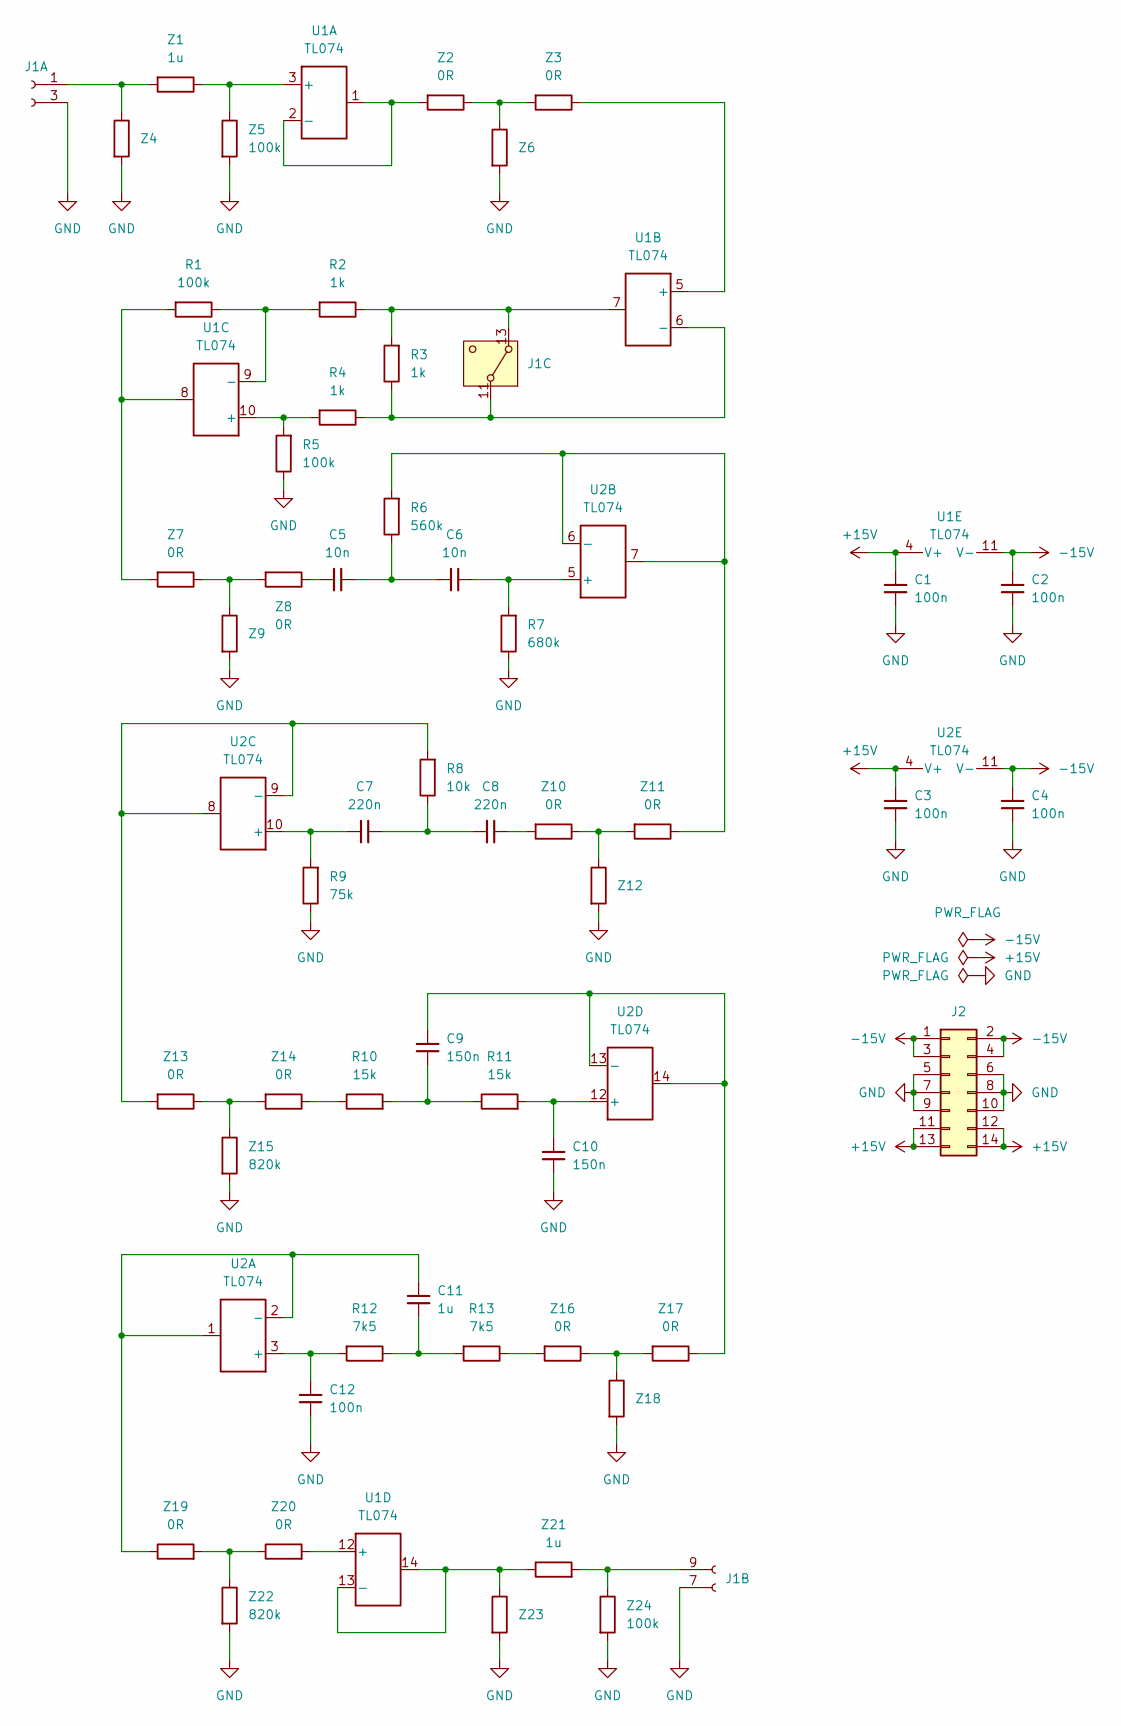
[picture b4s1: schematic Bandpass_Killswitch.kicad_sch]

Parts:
C1, C2, C3, C4, C12: 100n
C5, C6: 10n
C7, C8: 220n
C9, C10: 150n
C11: 1u
J1: Stecker_In_Out_Switch
J2: Conn_02x07_Odd_Even
R1, R5: 100k
R2, R3, R4: 1k
R6: 560k
R7: 680k
R8: 10k
R9: 75k
R10, R11: 15k
R12, R13: 7k5
U1, U2: TL074
Z1, Z21: 1u
Z2, Z3, Z7, Z8, Z10, Z11, Z13, Z14, Z16, Z17, Z19, Z20: 0R
Z4, Z6, Z9, Z12, Z18, Z23: (no value)
Z5, Z24: 100k
Z15, Z22: 820k

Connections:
+15V: C1.2, C3.2, J2.11, J2.12, J2.13, J2.14, U1.4 (V+), U2.4 (V+)
-15V: C2.2, C4.2, J2.1, J2.2, J2.3, J2.4, U1.11 (V-), U2.11 (V-)
GND: C1.1, C2.1, C3.1, C4.1, C10.1, C12.1, J1.3, J1.4, J1.5, J1.6, J1.7, J1.8, J2.5, J2.6, J2.7, J2.8, J2.9, J2.10, R5.1, R7.1, R9.1, Z4.2, Z5.2, Z6.2, Z9.2, Z12.2, Z15.2, Z18.2, Z22.2, Z23.2, Z24.2
unnamed: C5.1, Z8.1
unnamed: C5.2, C6.1, R6.1
unnamed: C7.1, C8.2, R8.1
unnamed: C8.1, Z10.2
unnamed: C9.1, R10.2, R11.1
unnamed: C11.1, R12.1, R13.2
unnamed: J1.1, J1.2, Z1.2, Z4.1
unnamed: J1.9, J1.10, Z21.2, Z24.1
unnamed: J1.11 (SW_In), J1.12, R3.1, R4.1, U1.6 (-)
unnamed: J1.13 (SW_Out), J1.14, R2.1, R3.2, U1.7
unnamed: R1.2, U1.8, Z7.2
unnamed: R10.1, Z14.1
unnamed: R13.1, Z16.2
unnamed: U1.3 (+), Z1.1, Z5.1
unnamed: U1.1, U1.2 (-), Z2.2
unnamed: U1.5 (+), Z3.1
unnamed: R4.2, R5.2, U1.10 (+)
unnamed: R1.1, R2.2, U1.9 (-)
unnamed: U1.12 (+), Z20.2
unnamed: U1.13 (-), U1.14, Z21.1, Z23.1
unnamed: C12.2, R12.2, U2.3 (+)
unnamed: C11.2, U2.1, U2.2 (-), Z19.1
unnamed: C6.2, R7.2, U2.5 (+)
unnamed: R6.2, U2.6 (-), U2.7, Z11.1
unnamed: C7.2, R9.2, U2.10 (+)
unnamed: R8.2, U2.8, U2.9 (-), Z13.2
unnamed: C10.2, R11.2, U2.12 (+)
unnamed: C9.2, U2.13 (-), U2.14, Z17.1
unnamed: Z2.1, Z3.2, Z6.1
unnamed: Z7.1, Z8.2, Z9.1
unnamed: Z10.1, Z11.2, Z12.1
unnamed: Z13.1, Z14.2, Z15.1
unnamed: Z16.1, Z17.2, Z18.1
unnamed: Z19.2, Z20.1, Z22.1
